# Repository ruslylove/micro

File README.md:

# AVR Microcontroller and Embedded Systems - Lecture Slides

This repository contains lecture slides for a microcontroller course based on
**"The AVR Microcontroller and Embedded Systems Using Assembly and C"**
by Mazidi, Naimi & Naimi.

**Instructor:** Dr. Ruslee Sutthaweekul

These slides are built using [Slidev](https://sli.dev), an open-source slide deck generator for developers.

## Course Content

Chapters 0-6 of the textbook:

*   **Chapter 0:** Introduction to Computing (number systems, logic gates, memory, CPU architecture)
*   **Chapter 1:** The AVR Microcontroller: History and Features
*   **Chapter 2:** AVR Architecture and Assembly Language Programming
*   **Chapter 3:** Branch, Call, and Time Delay Loop
*   **Chapter 4:** AVR I/O Port Programming
*   **Chapter 5:** Arithmetic, Logic Instructions, and Programs
*   **Chapter 6:** AVR Advanced Assembly Language Programming

## How to View the Slides

Live version: https://ruslylove.github.io/micro/

To run the interactive slide show on your local machine, you need Node.js installed.

1.  **Clone the repository:**
    ```bash
    git clone https://github.com/ruslylove/micro.git
    cd micro
    ```
2.  **Install dependencies:**
    ```bash
    npm install
    ```
3.  **Start the presentation:**
    ```bash
    npm run dev
    ```
4.  Open your browser and navigate to `http://localhost:3030`.

## Deployment

Pushes to `main` automatically build and deploy the slides to GitHub Pages via
`.github/workflows/deploy.yml`. Include `[pdf]` in a commit message (or run the
workflow manually) to also (re)export `slides.pdf`.

## License

The content and code examples in this repository are provided for educational purposes.

---

Learn more about Slidev at the official documentation.

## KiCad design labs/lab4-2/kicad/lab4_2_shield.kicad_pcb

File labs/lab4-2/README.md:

# Lab 4-2 KiCad Project

`kicad/lab4_2_shield.{kicad_pro,kicad_sch,kicad_pcb}` is a generated starting point for the
Lab 4-2 shield: the exact Lab 4-1 circuit (buttons, LEDs, multiplexed 7-segment displays,
digit-select transistors) captured as a schematic and laid out on a real Arduino Uno R3
shield outline. It was built programmatically (not drawn by hand in the KiCad GUI), using
dimensions and symbol/footprint geometry pulled from KiCad's own official libraries rather
than guessed, for exactly the reason the lab warns about: the shield header gap is a
real, documented quirk, not something to eyeball.

No KiCad installation was available while generating this, so **nothing here has been
opened in real KiCad, run through ERC/DRC, or plotted**. Treat it as a strong, verified
head start -- not a finished, fab-ready board. See "What to check first" below.

## What's authoritative vs. generated

- **Board outline, 4 mounting holes, and the 4 shield header positions** (including the
  famous non-0.1"-pitch gap between the Digital(0-7) and Digital(8-13) headers) come
  directly from KiCad's own official `Arduino_As_Uno_R3` PCB template
  (`kicad-library` repo) and the `Arduino_UNO_R3_WithMountingHoles` footprint
  (`kicad-footprints` repo) -- the same authoritative sources the lab tells you to use
  instead of a plain 0.1" header. The gap works out to 4.064 mm pin-to-pin (0.16"), i.e.
  1.524 mm (0.06") more than the standard 2.54 mm (0.1") pitch.
- All symbols (`Device:R`, `Device:LED`, `Device:Q_NPN`, `Switch:SW_Push`, `power:GND`,
  `Connector_Generic:Conn_01x0N`) and footprints (`Resistor_THT`, `LED_THT`,
  `Button_Switch_THT`, `Package_TO_SOT_THT`, `Resistor_THT` axial vertical) were copied
  from KiCad's current official symbol/footprint libraries, so they match what a real
  KiCad 10 install ships.
- **The 7-segment display symbol/footprint (`lab4_2_shield:DISPLAY_7SEG_CC`) is a
  hand-made placeholder.** KiCad's official symbol library ships no 7-segment display at
  all (confirmed by checking the library index), which is exactly why the lab tells you to
  search for one and verify it. This project's version has 10 pins (`a`-`g`, `cc1`, `cc2`,
  `dp`) with an arbitrary-but-documented pin order, and a footprint pad pattern borrowed
  from a real compact THT display (Broadcom HDSP-7401-style, 2x5 pins, 2.54 mm pitch).
  **Before you build: get your actual display's datasheet, confirm its real pin-out, and
  update the symbol pin names/footprint pad map to match** -- do not assume this one is
  right for your part. This is the single most important manual check in this repo.

## Circuit captured (identical to Lab 4-1)

| Signal | Uno pin | Net name(s) in the files |
|---|---|---|
| SW1-SW4 | D8-D11 | `D8`..`D11` |
| LED1-LED5 (through 330R) | D3-D7 | `D3_R1`..`D7_R5`, `LED1_A`..`LED5_A` |
| Segments a-f (through 330R) | A0-A5 | `SEGBUS_A`..`SEGBUS_F`, `A0_R6`..`A5_R11` |
| Segment g (through 330R) | D2 | `SEGBUS_G`, `D2_R12` |
| Digit-select bases (through 1k) | D12, D13 | `D12_R13`/`Q1_BASE`, `D13_R14`/`Q2_BASE` |
| Common ground return | Digital(8-13) header pin 2 | `GND` |

The Power header (J3) is placed for mechanical shield compliance but is **fully
unconnected** electrically, matching the lab's own note that only one GND path
(Digital(8-13) here) is needed. `AREF`, `D0`/`D1` (USB-serial), and the Power header's
`IOREF`/`RESET`/`3V3`/`5V`/`VIN`/`GND` pins are marked no-connect, same as Lab 4-1.

## What's routed on the PCB, and what's deliberately left for you

- The **board outline, mounting holes, and all four header footprints** are placed at the
  verified authoritative positions.
- **Every other footprint** (both displays, all 4 buttons, all 5 LEDs, both transistors,
  all 14 resistors) is placed with a verified-by-script non-overlapping layout, and every
  pad already carries its correct net -- so opening the PCB shows a full, correct ratsnest.
- A **GND copper zone** on the bottom layer (`B.Cu`) is defined covering most of the board
  interior; it should pick up every ground pad (button commons, LED cathodes, transistor
  emitters, the header's GND pin) once you fill zones (`B`, or Edit > Fill All Zones) --
  no manual GND routing needed.
- **No signal traces are pre-routed.** That's intentional, not an oversight: the lab's own
  Exercise 3 callout asks you to look at the ratsnest and predict which net is hardest to
  route (its own suggested answer is the 7-segment shared-segment bus -- 7 nets fanning out
  to 14 pads across two displays) *before* routing it yourself. Handing you a fully-routed
  board would remove exactly the exercise the lab is testing. Everything you need to route
  it correctly -- outline, headers, footprints, and a correct netlist -- is already here.

## What to check first (in order)

1. Open the project in KiCad 10. In the **Schematic Editor**, run **Tools > Annotate
   Schematic** if asked (power symbol references were pre-numbered `#PWR001..#PWR011`,
   but let KiCad confirm), then run **ERC**. Expect it to be clean except possibly
   "input pin not driven" warnings on the header nets -- that's expected and not a wiring
   bug: this schematic deliberately has no Arduino/MCU symbol (it's a peripheral-only
   shield, per the lab), so nothing in-sheet "drives" the header pins. You can lower that
   rule's severity in Schematic Setup if it's noisy.
2. Fix the 7-segment display pin-out (see above) against your actual part's datasheet.
3. In the **PCB Editor**, confirm the board outline and header positions visually match
   an authoritative Arduino Uno shield drawing, then **Fill Zones** and run **DRC**.
4. Route the remaining nets, using the lab's own trace/predict exercise as your guide.
   Then re-run DRC until clean.
5. Gerbers/drill files are **not** included -- that requires KiCad's own plot engine,
   which wasn't available while generating this project. Use File > Fabrication Outputs
   in the PCB Editor once routing is done.

## Viewing it in 3D

All resistors, LEDs, push buttons, and the two transistors have KiCad's stock 3D models
attached (from `Resistor_THT`, `LED_THT`, `Button_Switch_THT`, `Package_TO_SOT_THT`), so
`View > 3D Viewer` (Alt+3) in the PCB Editor will render them. The two shield headers and
the 7-segment displays are custom footprints with no stock 3D shape, so they'll show as
bare pads/outline in the 3D view -- that's expected, not a missing step.

## Files

```
kicad/lab4_2_shield.kicad_pro   project settings (net classes: 0.2mm clearance, 0.3mm track)
kicad/lab4_2_shield.kicad_sch   schematic (self-contained; all symbols embedded)
kicad/lab4_2_shield.kicad_pcb   PCB (self-contained; all footprints embedded)
```

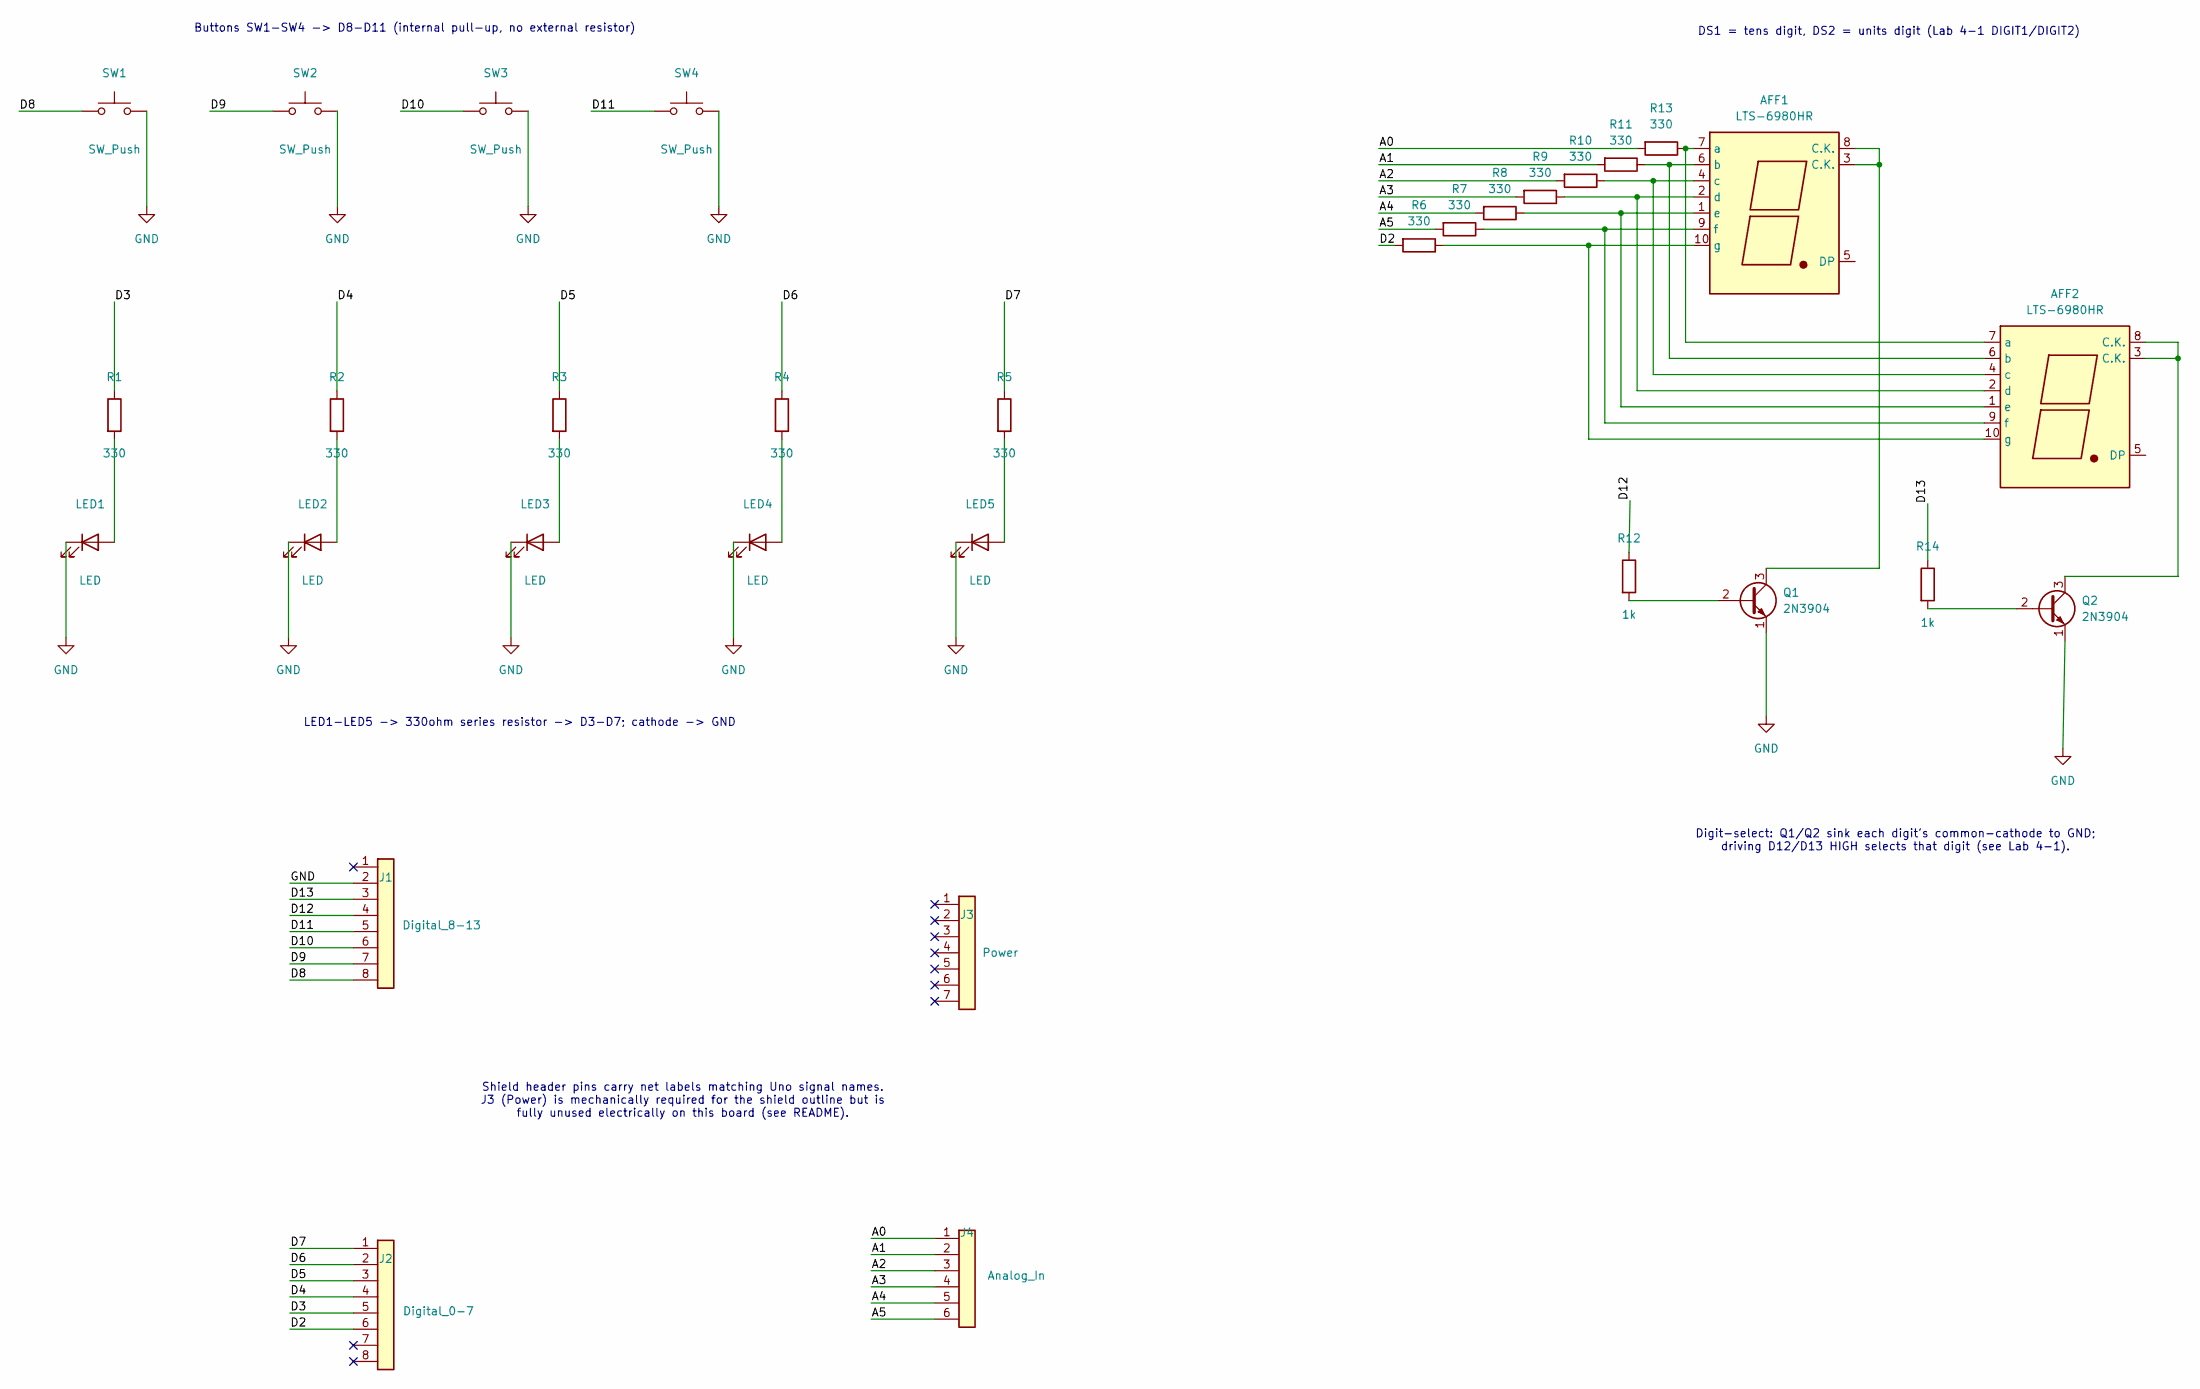
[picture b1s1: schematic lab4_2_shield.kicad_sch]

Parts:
AFF1, AFF2: LTS-6980HR; 7SegmentLED_LTS6760_LTS6780
J1: Digital_8-13; PinHeader_1x08_P2.54mm_Vertical
J2: Digital_0-7; PinHeader_1x08_P2.54mm_Vertical
J3: Power; PinHeader_1x07_P2.54mm_Vertical
J4: Analog_In; PinHeader_1x06_P2.54mm_Vertical
LED1, LED2, LED3, LED4, LED5: LED; LED_D5.0mm
Q1, Q2: 2N3904; TO-92_Inline
R1, R2, R3, R4, R5, R6, R7, R8, R9, R10, R11, R13: 330; R_Axial_DIN0207_L6.3mm_D2.5mm_P10.16mm_Horizontal
R12, R14: 1k; R_Axial_DIN0207_L6.3mm_D2.5mm_P10.16mm_Horizontal
SW1, SW2, SW3, SW4: SW_Push; SW_PUSH_6mm

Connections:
/A0: J4.1, R13.2
/A1: J4.2, R11.2
/A2: J4.3, R10.2
/A3: J4.4, R9.2
/A4: J4.5, R8.2
/A5: J4.6, R7.2
/D2: J2.6, R6.2
/D3: J2.5, R1.1
/D4: J2.4, R2.1
/D5: J2.3, R3.1
/D6: J2.2, R4.1
/D7: J2.1, R5.1
/D8: J1.8, SW1.1
/D9: J1.7, SW2.1
/D10: J1.6, SW3.1
/D11: J1.5, SW4.1
/D12: J1.4, R12.1
/D13: J1.3, R14.1
GND: J1.2, LED1.1 (K), LED2.1 (K), LED3.1 (K), LED4.1 (K), LED5.1 (K), Q1.1 (E), Q2.1 (E), SW1.2, SW2.2, SW3.2, SW4.2
unnamed: AFF1.7 (a), AFF2.7 (a), R13.1
unnamed: AFF1.6 (b), AFF2.6 (b), R11.1
unnamed: AFF1.4 (c), AFF2.4 (c), R10.1
unnamed: AFF1.2 (d), AFF2.2 (d), R9.1
unnamed: AFF1.1 (e), AFF2.1 (e), R8.1
unnamed: AFF1.9 (f), AFF2.9 (f), R7.1
unnamed: AFF1.10 (g), AFF2.10 (g), R6.1
unnamed: LED1.2 (A), R1.2
unnamed: LED2.2 (A), R2.2
unnamed: LED3.2 (A), R3.2
unnamed: LED4.2 (A), R4.2
unnamed: LED5.2 (A), R5.2
unnamed: Q1.2 (B), R12.2
unnamed: AFF1.3 (C.K.), AFF1.8 (C.K.), Q1.3 (C)
unnamed: Q2.2 (B), R14.2
unnamed: AFF2.3 (C.K.), AFF2.8 (C.K.), Q2.3 (C)

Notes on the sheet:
Digit-select: Q1/Q2 sink each digit's common-cathode to GND; driving D12/D13 HIGH selects that digit (see Lab 4-1).
Buttons SW1-SW4 -> D8-D11 (internal pull-up, no external resistor)
Shield header pins carry net labels matching Uno signal names. J3 (Power) is mechanically required for the shield outline but is fully unused electrically on this board (see README).
LED1-LED5 -> 330ohm series resistor -> D3-D7; cathode -> GND
DS1 = tens digit, DS2 = units digit (Lab 4-1 DIGIT1/DIGIT2)

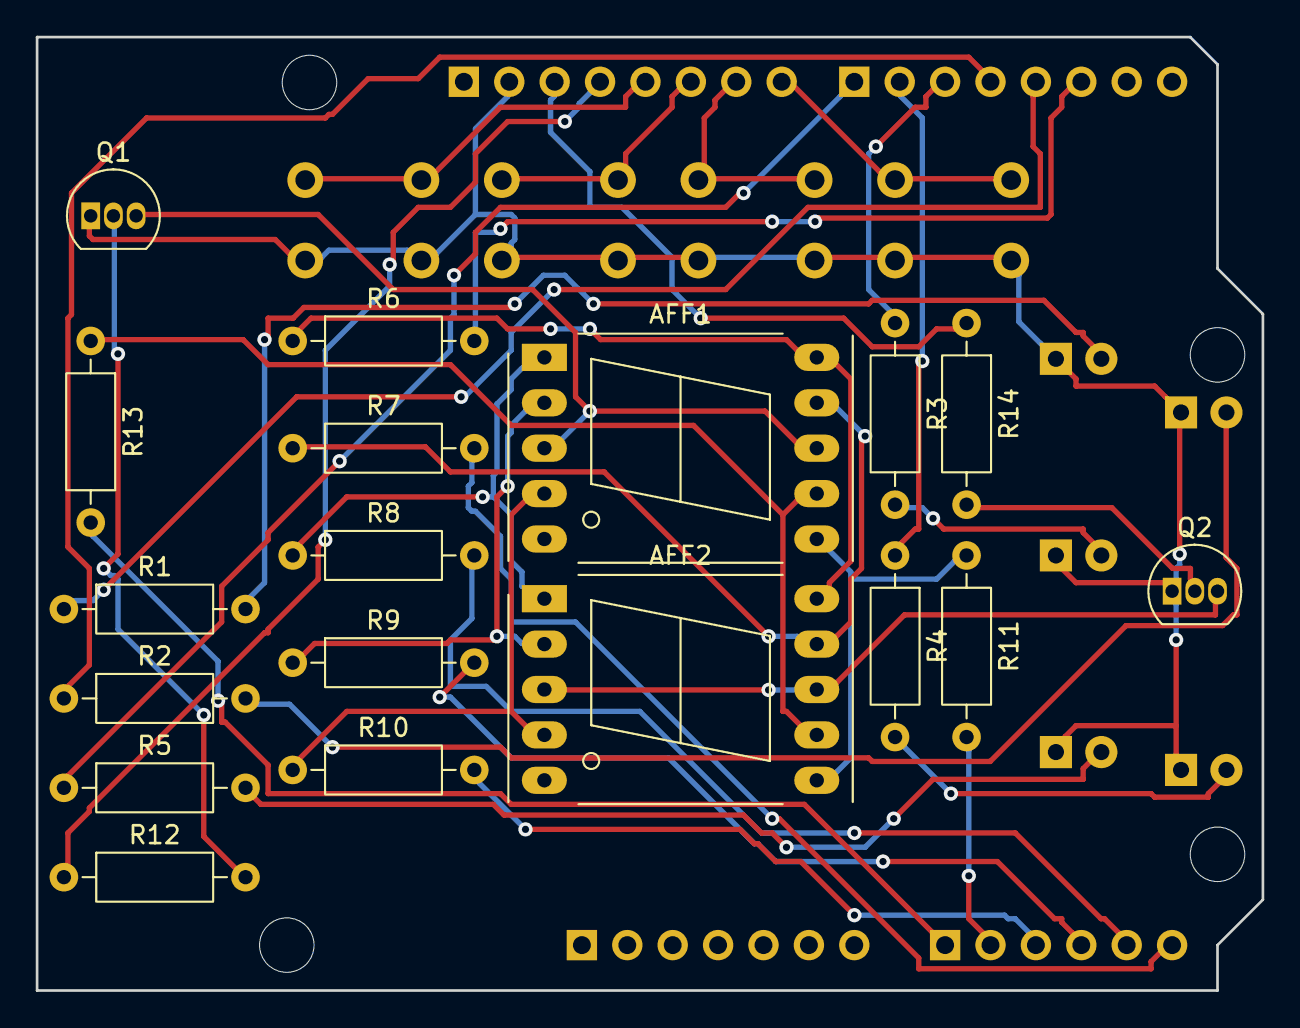
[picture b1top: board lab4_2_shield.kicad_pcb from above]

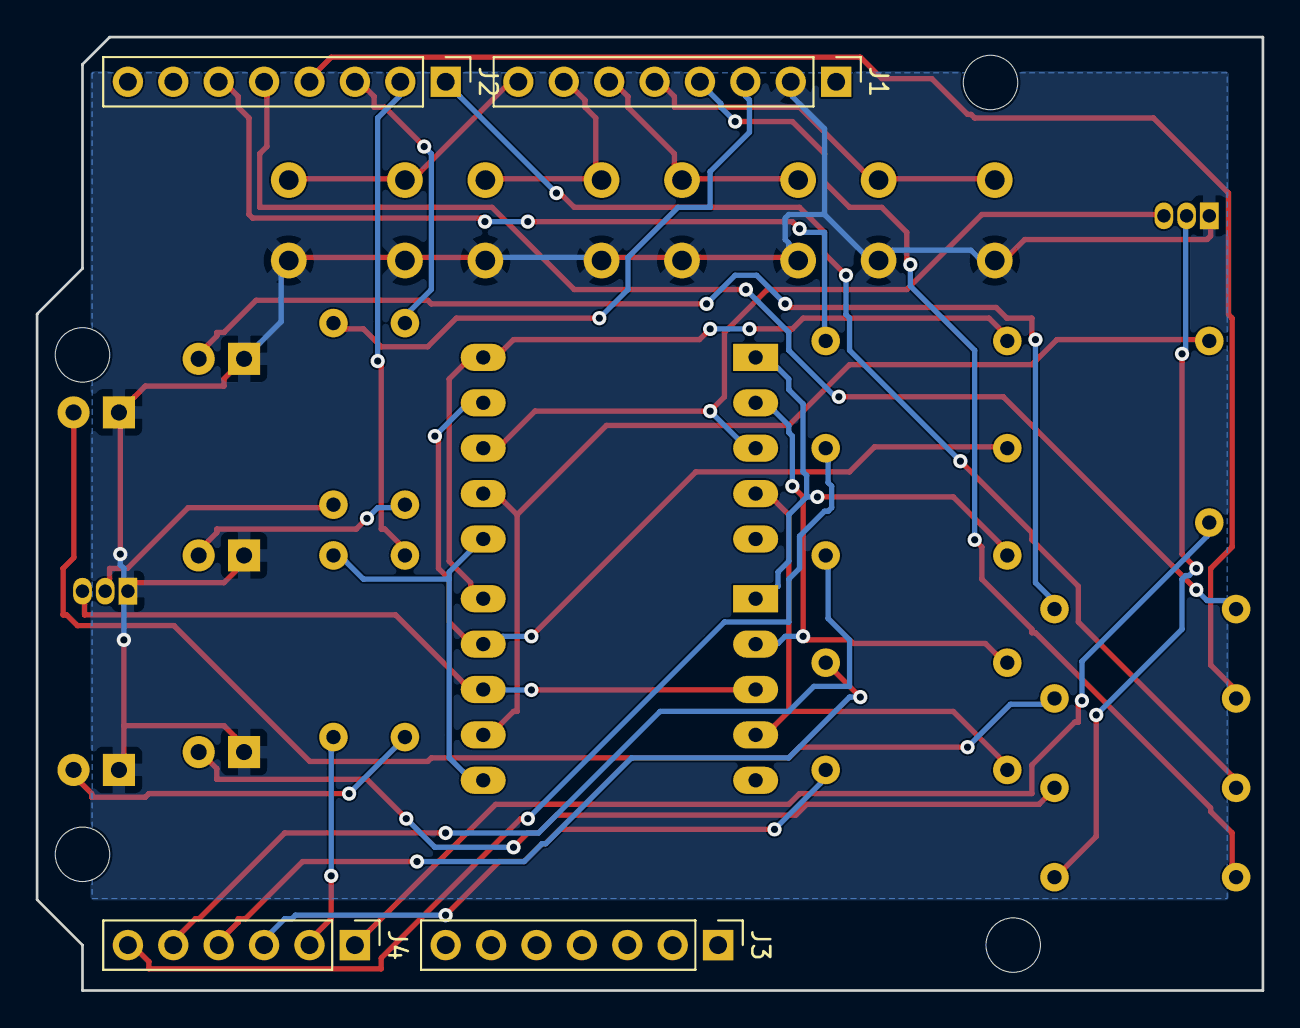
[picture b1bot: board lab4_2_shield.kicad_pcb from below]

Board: 2 copper layers, 68.6 x 53.3 mm, 31 parts (4 on the bottom side), 35 nets.

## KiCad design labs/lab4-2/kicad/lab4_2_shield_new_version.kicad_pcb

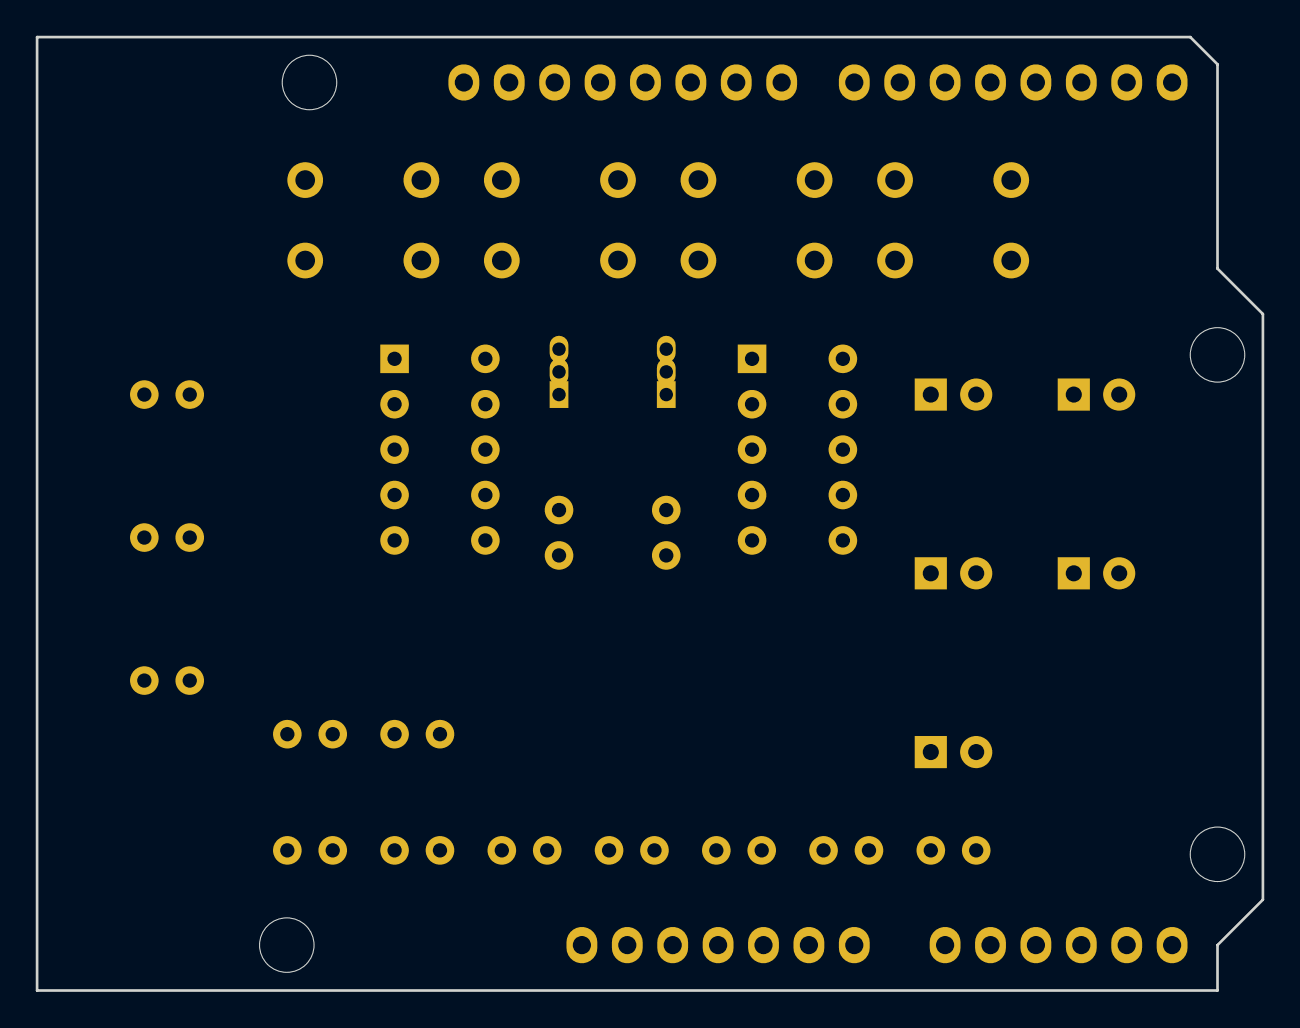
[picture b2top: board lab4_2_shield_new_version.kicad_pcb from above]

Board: 2 copper layers, 68.6 x 53.3 mm, 31 parts (0 on the bottom side), 35 nets, no tracks yet.

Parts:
DS1, DS2: 7SEG_CC_GENERIC_VERIFY_PINOUT; DISPLAY_7SEG_CC_GENERIC
J1: Digital_0-7; Header_Shield_Female_1x08_P2.54mm
J2: Digital_8-13; Header_Shield_Female_1x08_P2.54mm
J3: Power; Header_Shield_Female_1x07_P2.54mm
J4: Analog_In; Header_Shield_Female_1x06_P2.54mm
LED1, LED2, LED3, LED4, LED5: LED; LED_D5.0mm
Q1, Q2: 2N3904; TO-92_Inline
R1, R2, R3, R4, R5, R6, R7, R8, R9, R10, R11, R12: 330; R_Axial_DIN0207_L6.3mm_D2.5mm_P2.54mm_Vertical
R13, R14: 1k; R_Axial_DIN0207_L6.3mm_D2.5mm_P2.54mm_Vertical
SW1, SW2, SW3, SW4: SW_Push; SW_PUSH_6mm

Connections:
A0_R6: J4.1, R6.2
A1_R7: J4.2, R7.2
A2_R8: J4.3, R8.2
A3_R9: J4.4, R9.2
A4_R10: J4.5, R10.2
A5_R11: J4.6, R11.2
CC_DIG1: DS1.8, DS1.9, Q1.3
CC_DIG2: DS2.8, DS2.9, Q2.3
D2_R12: J1.6, R12.2
D3_R1: J1.5, R1.1
D4_R2: J1.4, R2.1
D5_R3: J1.3, R3.1
D6_R4: J1.2, R4.1
D7_R5: J1.1, R5.1
D8: J2.8, SW1.1
D9: J2.7, SW2.1
D10: J2.6, SW3.1
D11: J2.5, SW4.1
D12_R13: J2.4, R13.1
D13_R14: J2.3, R14.1
GND: J2.2, LED1.1, LED2.1, LED3.1, LED4.1, LED5.1, Q1.1, Q2.1, SW1.2, SW2.2, SW3.2, SW4.2
LED1_A: LED1.2, R1.2
LED2_A: LED2.2, R2.2
LED3_A: LED3.2, R3.2
LED4_A: LED4.2, R4.2
LED5_A: LED5.2, R5.2
Q1_BASE: Q1.2, R13.2
Q2_BASE: Q2.2, R14.2
SEGBUS_A: DS1.1, DS2.1, R6.1
SEGBUS_B: DS1.2, DS2.2, R7.1
SEGBUS_C: DS1.3, DS2.3, R8.1
SEGBUS_D: DS1.4, DS2.4, R9.1
SEGBUS_E: DS1.5, DS2.5, R10.1
SEGBUS_F: DS1.6, DS2.6, R11.1
SEGBUS_G: DS1.7, DS2.7, R12.1
